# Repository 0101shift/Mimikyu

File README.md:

# Mimikyu
Mimikyu is an e-Badge design inspired from Pokémon. The Badge embeds Attiny45 Micro-controller and Capacitive touch sensor for LED control (reverse mounted below eyes). The whole badge is powered by a 3V coin cell.

NOTE: BC547 pinout used in the design won't support SOT23 package, you may have to do some rework with TO-92 package.

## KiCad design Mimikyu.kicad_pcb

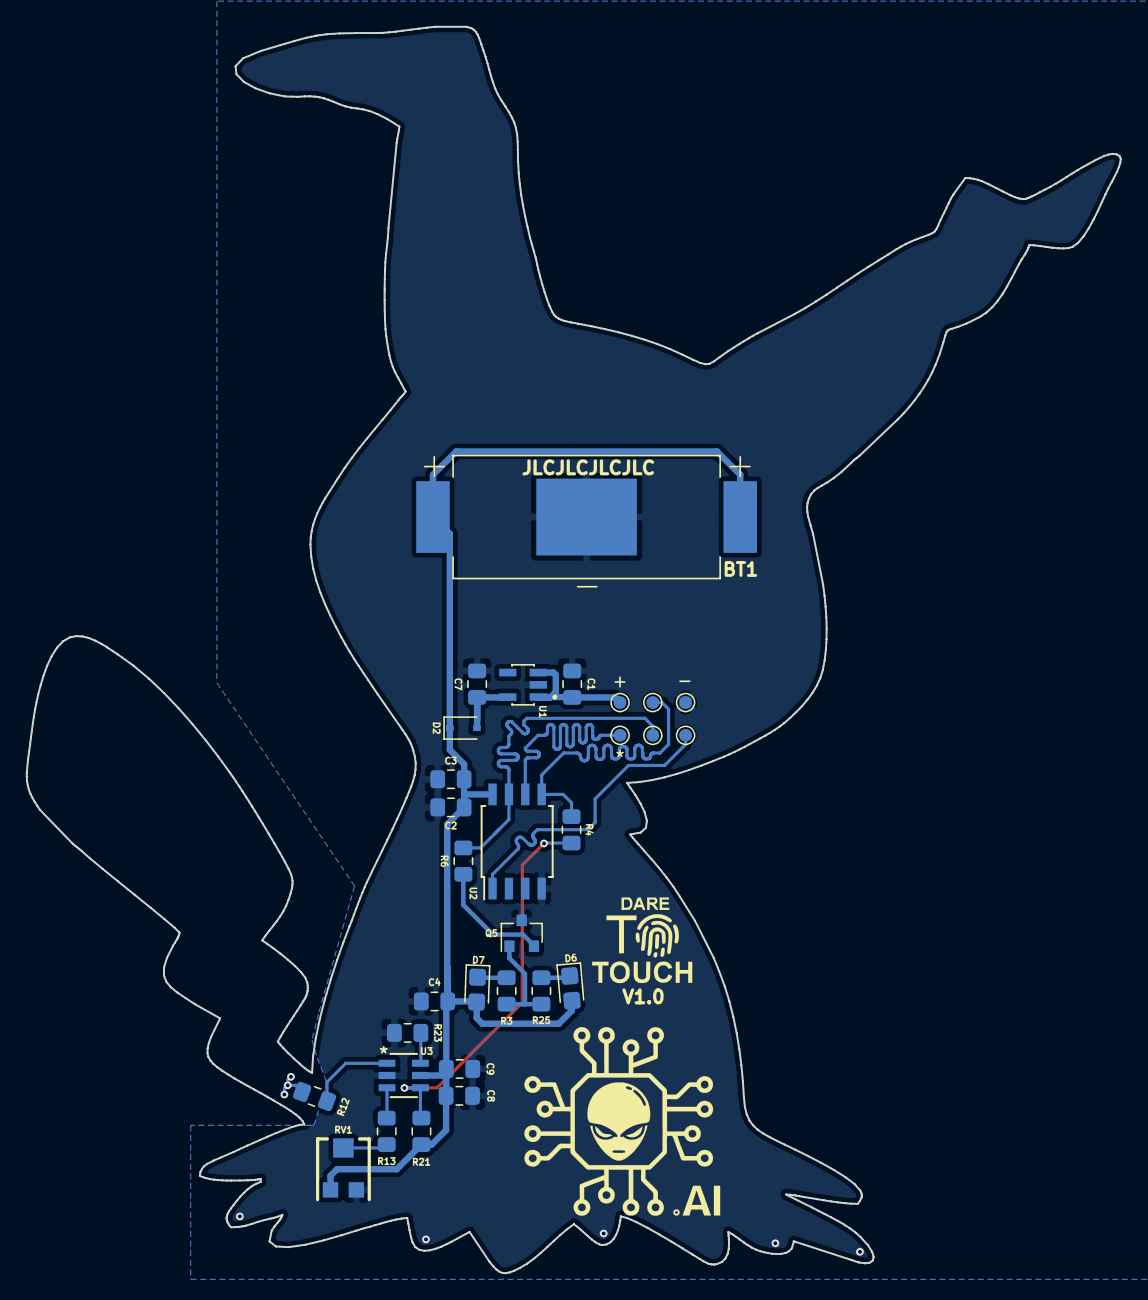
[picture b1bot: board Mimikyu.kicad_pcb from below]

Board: 2 copper layers, 84.8 x 96.6 mm, 30 parts (30 on the bottom side), 17 nets.

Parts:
BT1: BC-2003; BAT_BC-2003
C1, C7, C8: 1uF; C_0805_2012Metric_Pad1.15x1.40mm_HandSolder
C2: 4.7uF; C_0805_2012Metric_Pad1.15x1.40mm_HandSolder
C3, C9: 0.1uF; C_0805_2012Metric_Pad1.15x1.40mm_HandSolder
C4: 10uF; C_0805_2012Metric_Pad1.15x1.40mm_HandSolder
D2: D_Schottky; D_SOD-323
D6, D7: LED; LED_0805_2012Metric_Castellated
Q5: BC547; SOT-23
R3, R25: R; R_0805_2012Metric_Pad1.15x1.40mm_HandSolder
R4, R6, R13, R21, R23: 10K; R_0805_2012Metric_Pad1.15x1.40mm_HandSolder
R12: 4.7K; R_0805_2012Metric_Pad1.15x1.40mm_HandSolder
RV1: 10K; TC33X-2-103E
TP1, TP2, TP3, TP4, TP5, TP6: TestPoint; TestPoint_Pad_D1.0mm
U1: AP2112K-3.3TRG1
U2: ATtiny85-20SU; SOIJ-8_5.3x5.3mm_P1.27mm
U3: MTCH101T-I_OT; MTCH101T

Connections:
/5V_in: C1.1, TP5.1, U1.1, U1.3
/EYE_LED: Q5.2, R6.1
/MISO: TP2.1, U2.6
/MOSI: R4.2, TP3.1, U2.5
/MTO: R4.1, R21.2, U3.4
/MTPM: R23.1, U3.6
/MTSA: R13.1, RV1.2
/SCK: R6.2, TP4.1, U2.7
/Vin: BT1.S1+, BT1.S2+, C2.1, C3.1, C4.1, C8.1, C9.1, D2.1, D6.2, D7.2, R21.1, RV1.1, U2.8, U3.5
/rst: TP1.1, U2.1
GND: BT1.-, C1.2, C2.2, C3.2, C4.2, C7.2, C8.2, C9.2, Q5.3, R23.2, RV1.3, TP6.1, U1.2, U2.4, U3.2
unnamed: C7.1, D2.2, U1.5
unnamed: D6.1, R25.1
unnamed: D7.1, R3.1
unnamed: Q5.1, R3.2, R25.2
unnamed: R12.1, U3.1
unnamed: R13.2, U3.3

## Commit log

2022-06-18 Update README.md
    Added Image
2022-06-18 Add files via upload
    Added Project design files
2022-06-20 Add files via upload
    Added Design in .pdf

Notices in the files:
parts and their libraries:
Copyright 2016 Accelerated Designs. All rights reserved.
